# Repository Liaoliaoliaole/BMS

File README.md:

# BMS

# Project Structure

This repository contains the following directories to organize various aspects of the Battery Management System (BMS) project:
Meeting note and scrum report for scrum could be found from [Jira](https://liyuanliull.atlassian.net/jira/software/projects/SCRUM/boards/1/reports).

# `firmware`
The firmware directory includes the BMSServerApp source code. This application runs on the STM32L152RE Nucleo development board.   

## Cross-compilation
### Preconditions:
On Windows:   
- CMake
- Ninja
- STSW-LINK007
- GCC ARM None EABI Compiler

Details of the environment setup can be found in Confluence: [How-To-CrossCompile-BMSServerApp](https://liyuanliull.atlassian.net/wiki/spaces/BMSDEVELOP/pages/426109/How-to+Set+Up+Environment+and+Building+the+BMSServerApp)

### Build scripts
Navigate to the directory where the build script exists.   
Execute the following command in the terminal (such as Windows PowerShell):  
`./build_BMSServerApp.ps1 [-TestBuild]`   

- **Test Build**: Add the optional `-TestBuild` flag to include the testing features in your build, which will enable mock components or extra diagnostics during testing. For example:  
  `./build_BMSServerApp.ps1 -TestBuild`

Then connect the STM32L152RE to your PC, and run:    
`st-flash write BMSServerApp\build\BMSServerApp.bin 0x08000000`   

To remove the build, remove the `build` directory.

## GitHub Actions for CI/CD
The BMSServerApp project also supports automated builds via GitHub Actions. This allows you to build the project in the cloud whenever changes are pushed to the specified branch or a pull request is made.

### Build Types in GitHub Actions:
- The workflow is configured to build three different types: **Debug**, **Release**, and **Test**.
- The **Test** build defines a special `TEST` macro during compilation, enabling mock data and diagnostic features.

### How to Use GitHub Actions:
- **Trigger a Build**: Any push or pull request to the specified branch will automatically trigger the build process.
- **Check Build Status**: Monitor the status of the build in the "Actions" tab of the GitHub repository.
- **Find the Output**:   
  1. Click on the "Actions" tab.
  2. Select the Workflow Run: Find the specific workflow run to view its details.
  3. Scroll down to the "Artifacts" section on the workflow run page. This section shows the files that were uploaded during the workflow execution.
  4. Download the Binary File:  Click on the link for the binary file you want to download (e.g., `BMSServerApp-Debug-bin`, `BMSServerApp-Release-bin`, or `BMSServerApp-Test-bin`).   

# `prototyping`
This directory contains code, configurations, and other resources related to early-stage prototyping of the BMS project. It is used for experimenting with features, creating proof-of-concept implementations, and testing ideas before moving to production.  

- **Breadboard Prototyping**: The breadboard setup for the [current measurement module](https://liyuanliull.atlassian.net/wiki/spaces/BMSDEVELOP/pages/6520833/Voltage+Temperature+and+Current+measurement+Overview) and [temperature measurement prototypes](https://liyuanliull.atlassian.net/wiki/spaces/BMSDEVELOP/pages/8257538/Temperature+Measurement+Module+Prototyping+Documentation.) are stored in confluence.   
- **Calibration Functions**: Software calibration functions are developed to accommodate real-world measurements from the hardware prototypes, especially for [current mesurement](https://liyuanliull.atlassian.net/wiki/spaces/BMSDEVELOP/pages/19791874/Current+measurement+prototyping+and+calibration+calculation).   
Detailed documentation can be found in Confluence.  

# `schematic`
The schematic directory contains electrical and hardware design files, including circuit layouts, component schematics, and PCB designs. These designs are created using KiCad 7.0 and include PCB design files as well. All hardware-related files are stored here for reference.   

# `simulation`
This folder contains simulation models, scripts, and testing environments used for validating the BMS design and performance before physical implementation. Files related to simulation tools, test cases, and results are stored here.   

LTSpice Simulations: Simulation files created in LTSpice are used to validate the electrical design prior to prototyping.   

# `test`
This directory contains both hardware and software test cases and configurations for validating the BMS system.   

**Hardware Testing**: Includes [test cases](https://liyuanliull.atlassian.net/wiki/spaces/BMSDEVELOP/pages/20250626/Hardware+testing+notes) and documentation for validating the physical components of the BMS system: mosfet board, main board, current measurement board and temperature measurement board.   

**Software Testing**: The software testing for the BMSServerApp and BMSClientApp was conducted using several approaches to ensure robust functionality and communication. Key testing scenarios include:     
- ADC Converter Testing: Simulated mock ADC values to validate the proper functioning of the ADC conversion process in the software, ensuring accurate data handling.   
- Modbus Communication Testing: Tested Modbus function code 04 to verify reliable communication between the server and client, ensuring proper data exchange over the Modbus protocol.   
- Grafana Visualization: Validated the integration with Grafana by verifying the display of MCU-sent values on the Grafana dashboard, ensuring accurate and real-time monitoring of system metrics.   
- MOSFET Control Scenarios: Tested various MOSFET control scenarios by simulating different voltage, current, and temperature conditions. This validated the software's ability to control MOSFETs based on these parameters, ensuring correct operation under varying environmental and system conditions.

Detailed results of these hardware and software tests can be found in test dir README.

# `views`
The BMS project uses Grafana for visualization. A short documentation on how to log in and set up Grafana dashboards for monitoring BMS metrics is provided.

### How to Use Grafana

**Logging in as Guest**
1. Access Grafana: Open your web browser and navigate to the [Grafana URL](http://16.16.145.115:3000/login).
2. Guest Login: On the login page use username *Grafana_Viewer* and password *8qr8MzZM*.
3. Browse Dashboards: As a guest, you will have read-only access to the dashboards. You can browse through the available visualizations, interact with the data by zooming in on graphs, and apply filters to view specific data ranges.

**Logging in as Admin**
1. Access Grafana: Open your web browser and navigate to the [Grafana URL](http://16.16.145.115:3000/login).
2. Admin Login: Enter the admin username and password. You can obtain this data on request.
3. Admin Dashboard: Once logged in, you will have full access to all Grafana features, including the ability to create, edit, and delete dashboards, manage data sources, and configure system settings.

**Adding New Visualizations**
1. Add a Panel: Click on "Add new panel" to start creating a new visualization.
2. Select Data Source: Choose the data source from which you want to pull data. This is BMS database in our case.
3. Configure Query: Write the query to fetch the data you need. 
4. Choose Visualization Type: Select the type of visualization you want to create, such as a graph, table or heatmap.
5. Save the Panel: Once you are satisfied with the configuration, click "Apply" to add the panel to your dashboard. Don't forget to save the dashboard itself to retain your changes.

### Testing

**For Test Purposes with Static Values Compile BMSServerApp (STM32) with Symbol TEST**

1. Open the BMSServerApp project in your IDE.
2. Locate the project settings where preprocessor symbols are defined. This is typically found under project properties or build settings.
3. Add the symbol `TEST` to the list of preprocessor definitions.
4. Build the project. This will generate the firmware binary with the test mode enabled.
5. Flash the compiled firmware onto the STM32 microcontroller using a programmer or debugger tool.
6. With the test firmware running, the BMSServerApp will use predefined static values instead of real sensor data, allowing you to test the system's functionality without needing actual sensor inputs.

**For Testing Grafana Without Using STM32 Run `test_data_generator.py` from Views Folder**

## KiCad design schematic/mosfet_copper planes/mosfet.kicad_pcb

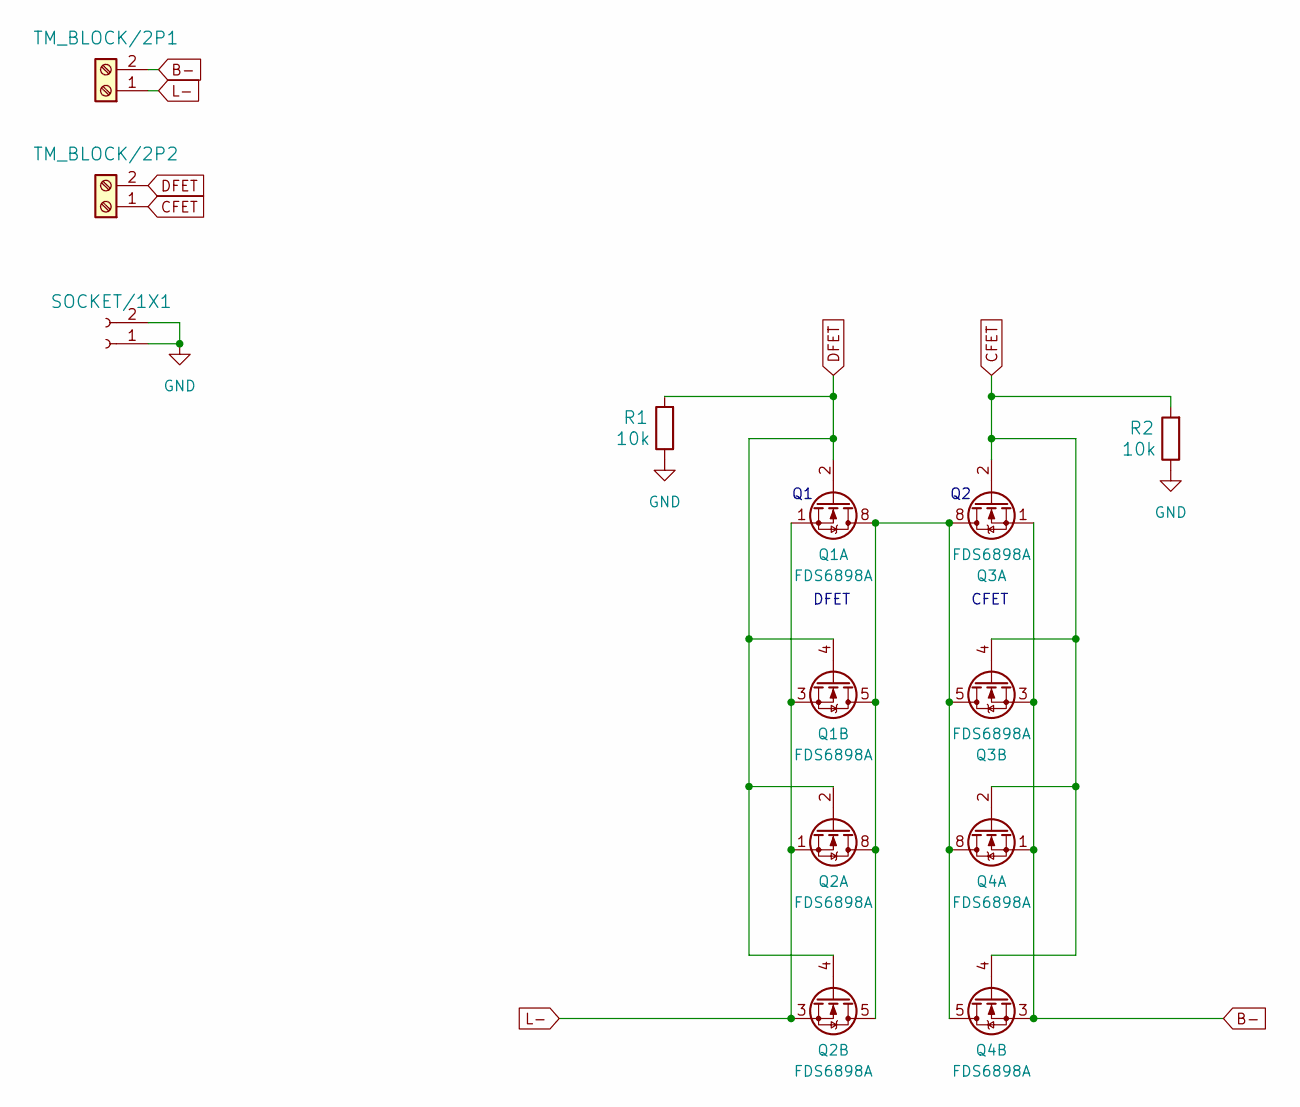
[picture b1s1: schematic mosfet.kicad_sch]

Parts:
Q1, Q2, Q3, Q4: FDS6898A; SOIC-8_3.9x4.9mm_P1.27mm
R1, R2: 10k; 1206; Tolerance +-5%
SOCKET/1X1: SOCKET_1X2; SOCKET_1x2
TM_BLOCK/2P1, TM_BLOCK/2P2: TM_BLOCK_2P

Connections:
B-: Q3.1 (S1), Q3.3 (S2), Q4.1 (S1), Q4.3 (S2), TM_BLOCK/2P1.2
CFET: Q3.2 (G1), Q3.4 (G2), Q4.2 (G1), Q4.4 (G2), R2.2, TM_BLOCK/2P2.1
DFET: Q1.2 (G1), Q1.4 (G2), Q2.2 (G1), Q2.4 (G2), R1.2, TM_BLOCK/2P2.2
GND: R1.1, R2.1, SOCKET/1X1.1, SOCKET/1X1.2
L-: Q1.1 (S1), Q1.3 (S2), Q2.1 (S1), Q2.3 (S2), TM_BLOCK/2P1.1
unnamed: Q1.5 (D2), Q1.6 (D2), Q1.7 (D1), Q1.8 (D1), Q2.5 (D2), Q2.6 (D2), Q2.7 (D1), Q2.8 (D1), Q3.5 (D2), Q3.6 (D2), Q3.7 (D1), Q3.8 (D1), Q4.5 (D2), Q4.6 (D2), Q4.7 (D1), Q4.8 (D1)

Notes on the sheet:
DFET
CFET

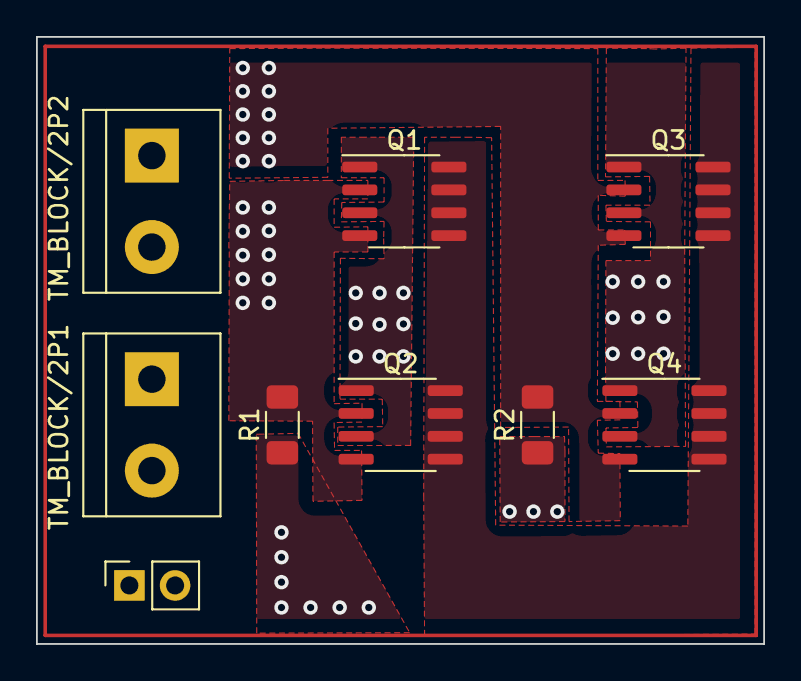
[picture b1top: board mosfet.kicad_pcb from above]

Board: 2 copper layers, 40.4 x 33.7 mm, 9 parts (0 on the bottom side), 6 nets.

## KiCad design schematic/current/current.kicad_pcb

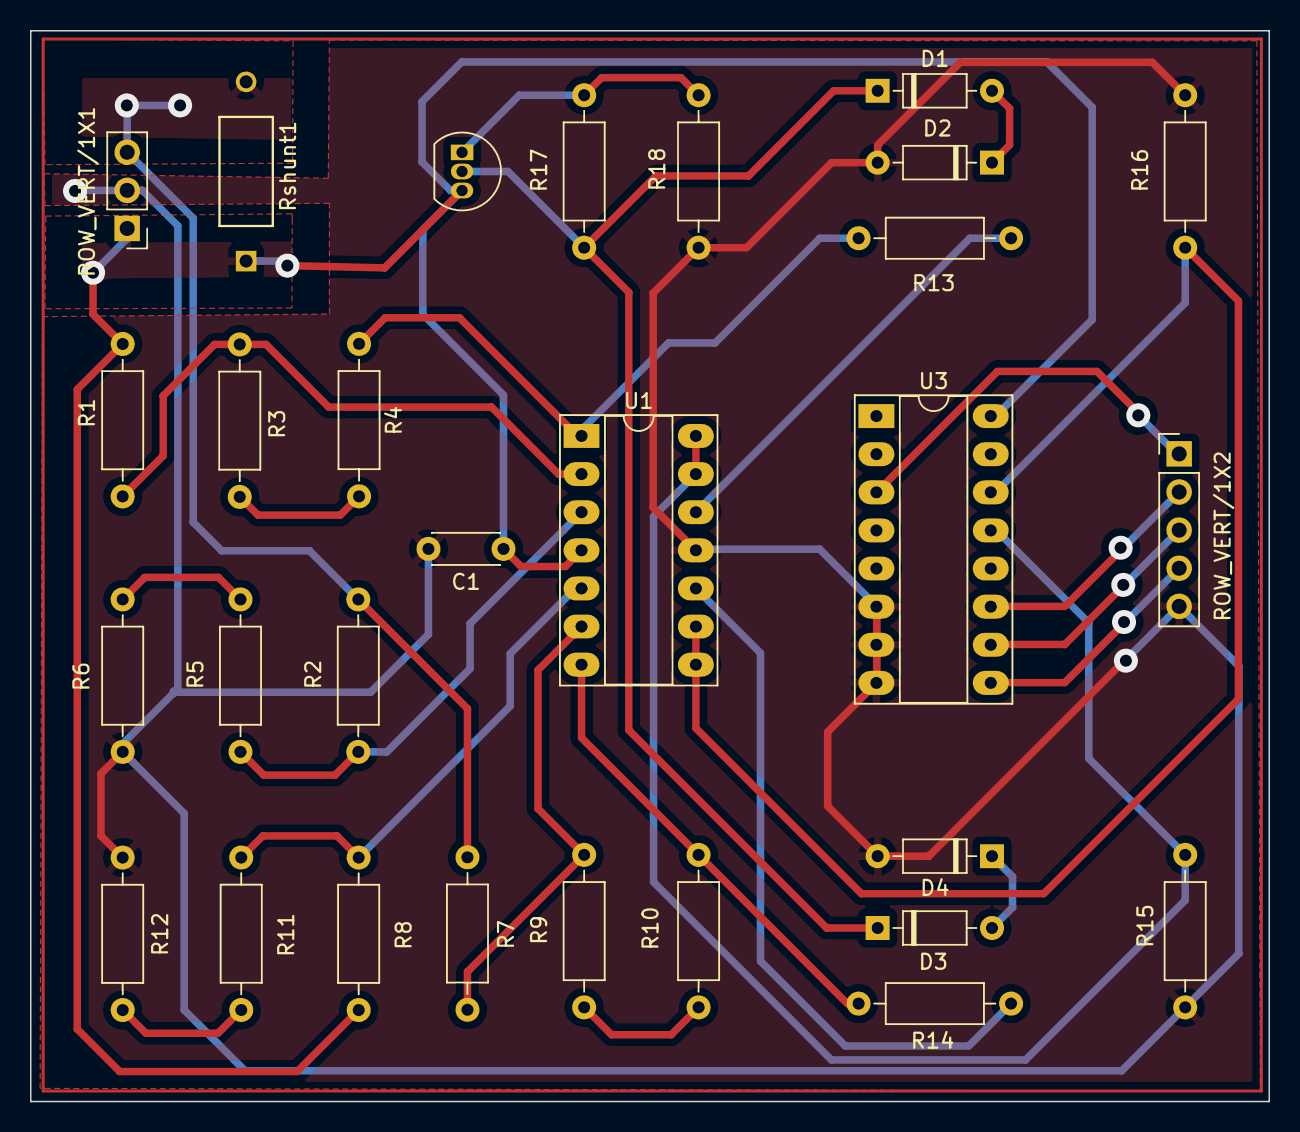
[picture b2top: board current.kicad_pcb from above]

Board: 2 copper layers, 82.5 x 71.4 mm, 29 parts (0 on the bottom side), 25 nets.

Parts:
C1: 100NF_50V_CER; C5_0
D1, D2, D3, D4: 1N4148; D_DO-35_SOD27_P7.62mm_Horizontal
R1, R2, R7, R8: 910R; R3_5W
R3, R5, R9, R11: 30k; R3_5W
R4, R6, R10, R12: 2k; R3_5W
R13, R14, R15, R16: 10k; R3_5W
R17: 470R; R3_5W
R18: 620R; R3_5W
ROW_VERT/1X1: ROW_VERT_1X3; ROW_VERT_1x3
ROW_VERT/1X2: ROW_VERT_1X5; ROW_VERT_1x5
Rshunt1: 0.01R; RES_WH&slash_NB_OHM
U1: LM324NE4; DIP-14_W7.62mm_Socket_LongPads
U2: LM317L_TO92; TO-92_Inline
U3: CD4051B; DIP-16_W7.62mm_Socket_LongPads

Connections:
+12V: C1.1, R1.1, R8.1, ROW_VERT/1X1.1, Rshunt1.1, U1.4, U2.3 (VI), U3.16 (VDD)
B+: R2.1, R7.1, ROW_VERT/1X1.3, Rshunt1.2
GND: C1.2, D2.2 (A), D4.2 (A), R6.1, R12.1, R15.1, R16.1, R18.1, ROW_VERT/1X1.2, ROW_VERT/1X2.5, U1.11, U3.6 (INH), U3.7 (VEE), U3.8 (VSS)
unnamed: D1.2 (A), D2.1 (K)
unnamed: D3.2 (A), D4.1 (K)
unnamed: R1.2, R3.1, U1.2
unnamed: R2.2, R5.2, U1.3
unnamed: R3.2, R4.1
unnamed: R5.1, R6.2
unnamed: R7.2, R9.1, U1.6
unnamed: R9.2, R10.1
unnamed: R11.1, R12.2
unnamed: R8.2, R11.2, U1.5
unnamed: R13.2, U1.12
unnamed: R14.2, U1.10
unnamed: R17.1, R18.2, U2.1 (ADJ)
unnamed: R15.2, U1.13, U1.14, U3.13 (X0)
unnamed: R16.2, U1.8, U1.9, U3.14 (X1)
V_ESD: D1.1 (K), D3.1 (K), R17.2, U2.2 (VO)
V_shunt: ROW_VERT/1X2.1, U3.3 (X)
V_shunt1: R4.2, R13.1, U1.1
V_shunt2: R10.2, R14.1, U1.7
sel_A: ROW_VERT/1X2.2, U3.11 (A)
sel_B: ROW_VERT/1X2.3, U3.10 (B)
sel_C: ROW_VERT/1X2.4, U3.9 (C)

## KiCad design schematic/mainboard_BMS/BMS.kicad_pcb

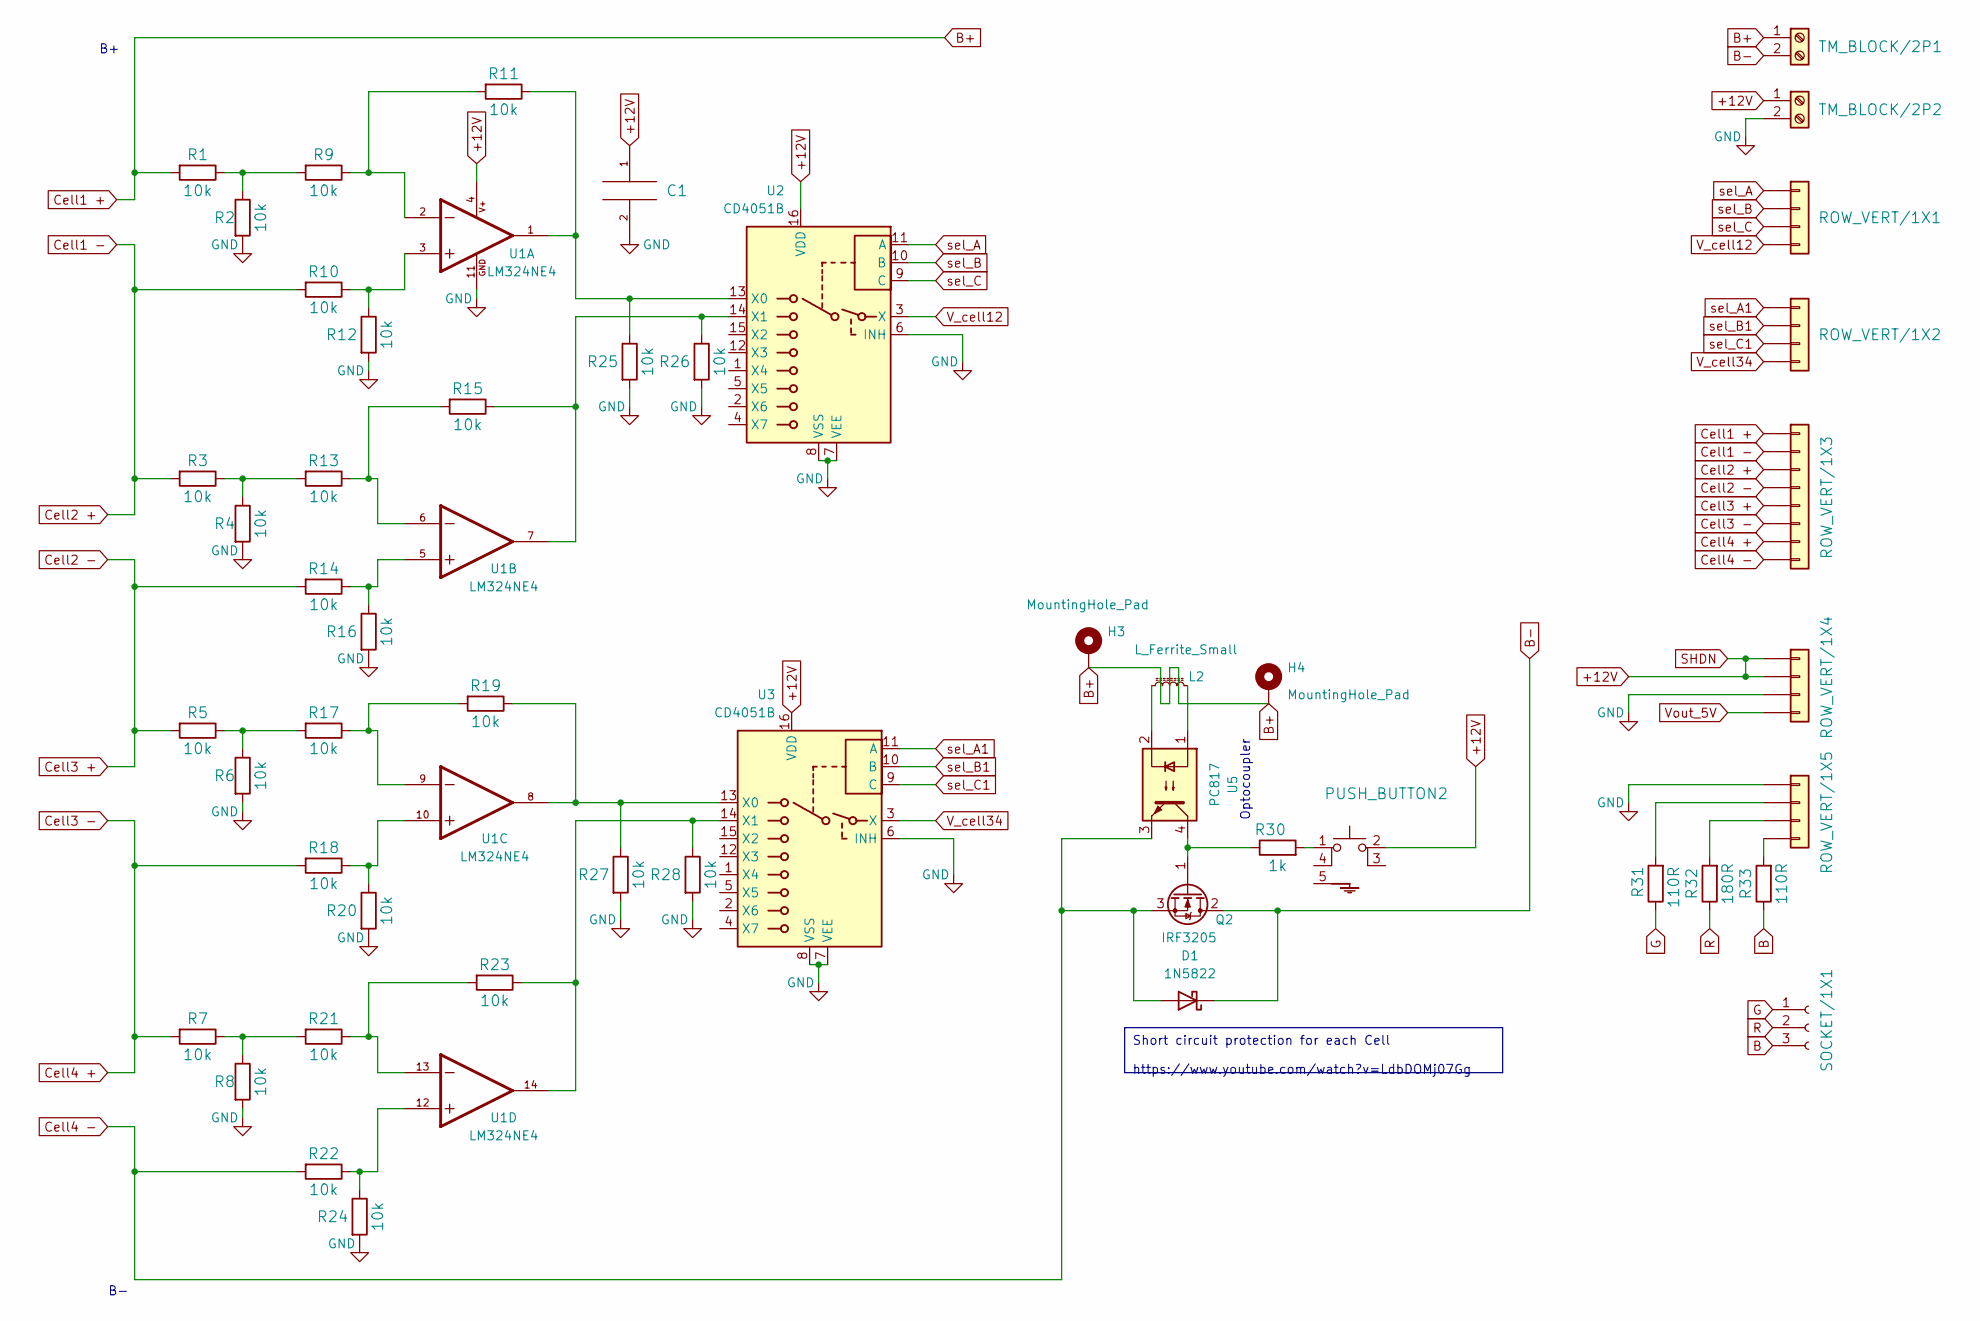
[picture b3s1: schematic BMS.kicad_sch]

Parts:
C1: 100NF_50V_CER; C5_0; Tolerance +-10%
D1: 1N5822; D_DO-201AD_P15.24mm_Horizontal
H3, H4: MountingHole_Pad; MountingHole_2.2mm_M2_Pad
L2: L_Ferrite_Small; PE92112KNL
PUSH_BUTTON2: PUSH_BUTTON; SKHHQV
Q2: IRF3205; TO-220-3_Vertical
R1, R2, R3, R4, R5, R6, R7, R8, R9, R10, R11, R12, R13, R14, R15, R16, R17, R18, R19, R20, R21, R22, R23, R24, R25, R26, R27, R28: 10k; R3_5W; Tolerance +-1%
R30: 1k; R3_5W; Tolerance +-1%
R31, R33: 110R; R3_5W; Tolerance +-1%
R32: 180R; R3_5W; Tolerance +-1%
ROW_VERT/1X1, ROW_VERT/1X2, ROW_VERT/1X4, ROW_VERT/1X5: ROW_VERT_1X4; ROW_VERT_1x4
ROW_VERT/1X3: ROW_VERT_1X8; ROW_VERT_1x8
SOCKET/1X1: SOCKET_1X3; SOCKET_1x3
TM_BLOCK/2P1, TM_BLOCK/2P2: TM_BLOCK_2P
U1: LM324NE4; DIP-14_W7.62mm_Socket_LongPads; PARTREV D
U2, U3: CD4051B; DIP-16_W7.62mm_Socket_LongPads
U5: PC817; DIP-4_W7.62mm

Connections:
+12V: C1.1, PUSH_BUTTON2.2 (A), ROW_VERT/1X4.1, ROW_VERT/1X4.2, TM_BLOCK/2P2.1, U1.4, U2.16 (VDD), U3.16 (VDD)
B: R33.1, SOCKET/1X1.3
B+: H3.1, H4.1, R1.2, ROW_VERT/1X3.1, TM_BLOCK/2P1.1
B-: D1.1 (K), Q2.2 (D), TM_BLOCK/2P1.2
Cell1 -: R3.2, R10.2, ROW_VERT/1X3.2, ROW_VERT/1X3.3
Cell2 -: R5.2, R14.2, ROW_VERT/1X3.4, ROW_VERT/1X3.5
Cell3 -: R7.2, R18.2, ROW_VERT/1X3.6, ROW_VERT/1X3.7
Cell4 -: D1.2 (A), Q2.3 (S), R22.2, ROW_VERT/1X3.8, U5.3
G: R31.1, SOCKET/1X1.1
GND: C1.2, R2.2, R4.2, R6.2, R8.2, R12.2, R16.2, R20.2, R24.2, R25.2, R26.2, R27.2, R28.2, ROW_VERT/1X4.3, ROW_VERT/1X5.1, TM_BLOCK/2P2.2, U1.11, U2.6 (INH), U2.7 (VEE), U2.8 (VSS), U3.6 (INH), U3.7 (VEE), U3.8 (VSS)
unnamed: L2.1, U5.2
unnamed: L2.2, U5.1
unnamed: PUSH_BUTTON2.1, R30.2
unnamed: Q2.1 (G), R30.1, U5.4
unnamed: R1.1, R2.1, R9.2
unnamed: R10.1, R12.1, U1.3
unnamed: R9.1, R11.2, U1.2
unnamed: R13.1, R15.2, U1.6
unnamed: R3.1, R4.1, R13.2
unnamed: R14.1, R16.1, U1.5
unnamed: R17.1, R19.2, U1.9
unnamed: R5.1, R6.1, R17.2
unnamed: R18.1, R20.1, U1.10
unnamed: R21.1, R23.2, U1.13
unnamed: R7.1, R8.1, R21.2
unnamed: R22.1, R24.1, U1.12
unnamed: R31.2, ROW_VERT/1X5.2
unnamed: R32.2, ROW_VERT/1X5.3
unnamed: R33.2, ROW_VERT/1X5.4
unnamed: R11.1, R25.1, U1.1, U2.13 (X0)
unnamed: R15.1, R26.1, U1.7, U2.14 (X1)
unnamed: R19.1, R27.1, U1.8, U3.13 (X0)
unnamed: R23.1, R28.1, U1.14, U3.14 (X1)
R: R32.1, SOCKET/1X1.2
V_cell12: ROW_VERT/1X1.4, U2.3 (X)
V_cell34: ROW_VERT/1X2.4, U3.3 (X)
Vout_5V: ROW_VERT/1X4.4
sel_A: ROW_VERT/1X1.1, U2.11 (A)
sel_A1: ROW_VERT/1X2.1, U3.11 (A)
sel_B: ROW_VERT/1X1.2, U2.10 (B)
sel_B1: ROW_VERT/1X2.2, U3.10 (B)
sel_C: ROW_VERT/1X1.3, U2.9 (C)
sel_C1: ROW_VERT/1X2.3, U3.9 (C)

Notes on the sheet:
Short circuit protection for each Cell https://www.youtube.com/watch?v=LdbDOMj07Gg
Optocoupler

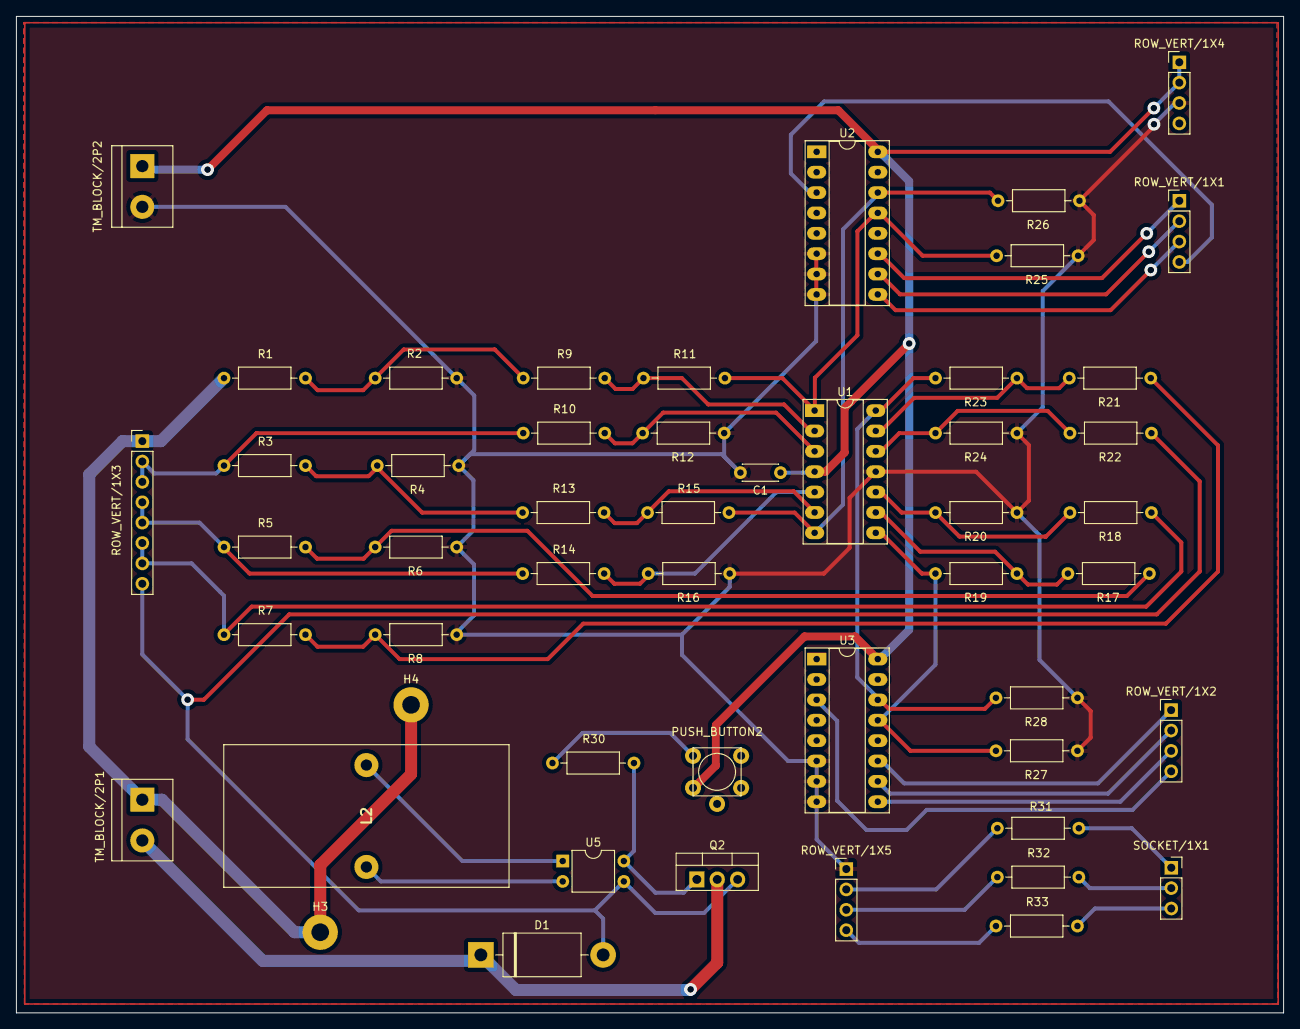
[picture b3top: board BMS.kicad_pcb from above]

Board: 2 copper layers, 158.0 x 124.2 mm, 51 parts (0 on the bottom side), 42 nets.

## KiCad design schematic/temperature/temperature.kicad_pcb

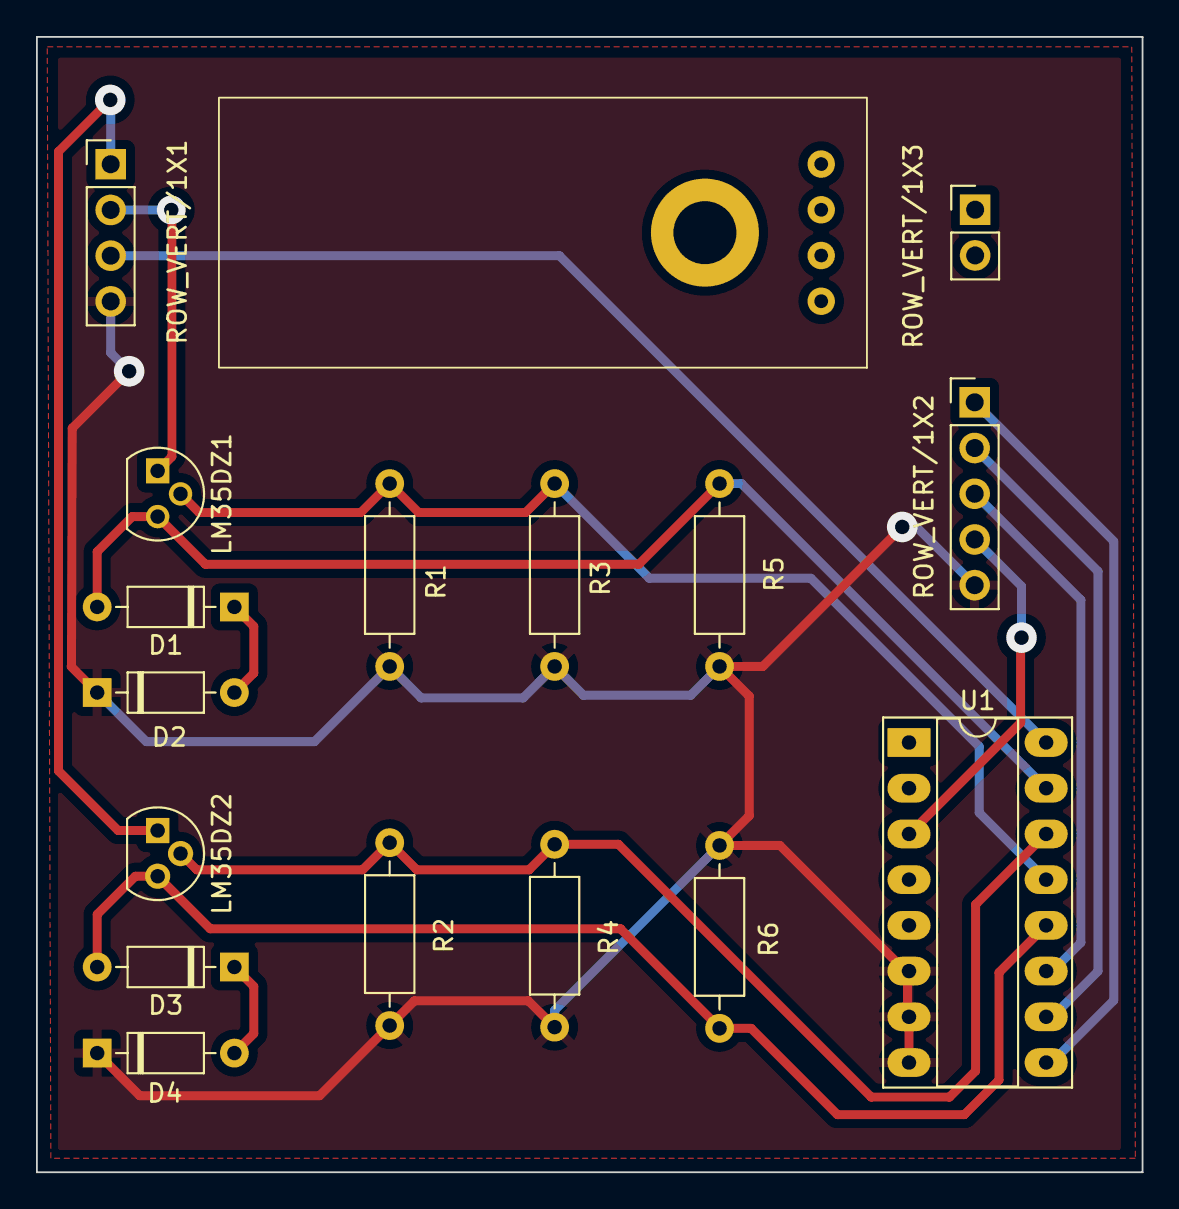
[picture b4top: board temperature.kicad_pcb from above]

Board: 2 copper layers, 61.4 x 63.1 mm, 17 parts (0 on the bottom side), 14 nets.

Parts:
A1: Flame_KY026; KY026
D1, D2, D3, D4: 1N4148; D_DO-35_SOD27_P7.62mm_Horizontal
LM35DZ1, LM35DZ2: LM35DZ_TO92; TO-92
R1, R2: 18k; R3_5W
R3, R4, R5, R6: 10k; R3_5W
ROW_VERT/1X1: ROW_VERT_1X4; ROW_VERT_1x4
ROW_VERT/1X2: ROW_VERT_1X5; ROW_VERT_1x5
ROW_VERT/1X3: ROW_VERT_1X2; ROW_VERT_1x2
U1: CD4051B; DIP-16_W7.62mm_Socket_LongPads

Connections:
+5V: ROW_VERT/1X1.3, U1.16 (VDD)
GND: D2.1 (K), D4.1 (K), R1.1, R2.1, R3.1, R4.1, R5.1, R6.1, ROW_VERT/1X1.4, ROW_VERT/1X2.5, U1.6 (INH), U1.7 (VEE), U1.8 (VSS)
unnamed: D1.2 (A), LM35DZ1.3 (GND), R5.2, U1.15 (X2)
unnamed: D1.1 (K), D2.2 (A)
unnamed: D3.2 (A), LM35DZ2.3 (GND), R6.2, U1.12 (X3)
unnamed: D3.1 (K), D4.2 (A)
unnamed: LM35DZ1.2 (Vout), R1.2, R3.2, U1.13 (X0)
unnamed: LM35DZ2.2 (Vout), R2.2, R4.2, U1.14 (X1)
V_cell12: LM35DZ1.1 (+VS), ROW_VERT/1X1.2
V_cell34: LM35DZ2.1 (+VS), ROW_VERT/1X1.1
V_temperature: ROW_VERT/1X2.4, U1.3 (X)
sel_A: ROW_VERT/1X2.3, U1.11 (A)
sel_B: ROW_VERT/1X2.2, U1.10 (B)
sel_C: ROW_VERT/1X2.1, U1.9 (C)

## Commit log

2024-09-08 Initial project structure setup
2024-09-08 Initialized bms project in truestudio.
    Issue : SCRUM-7
2024-09-09 SCRUM-6 Added a text file
2024-09-09 Meta info SCRUM-7
2024-09-09 Add test. Issue : SCRUM-5
2024-09-09 block diagram
2024-09-09 SCRUM-6 Text file added
2024-09-09 Ignore files in firmware/.metadata/. Add basic libs of stm32 functions.
    Issue : SCRUM-7
2024-09-09 SCRUM-5 add active balancing
2024-09-09 active balancing
2024-09-10 SCRUM-5 test
2024-09-10 Add LM324N opamp prototypying. Designed calibration method.
    Issue : SCRUM-5
2024-09-14 Add modbus slave lib, update ADC convert.
    Issue: SCRUM-7
2024-09-17 Add main supporting mock values using modbus RTU Function code 04 to communicate with test_slave. Add test_slave. Restructure include, src and libs.
    Issue: SCRUM-7
2024-09-18 Add multiplexer code. Tested with PA5 led blink to select channal. Issue: SCRUM-7
2024-09-19 active_balancing.jpg
2024-09-19 SCRUM-2 add draft schematic
2024-09-19 SCRUM-6 Added a python prototype file for grafana usage
2024-09-19 SCRUM-5 add new block diagram
2024-09-21 Create cross-compilation steps using cmake and ninja. Updated README for relevant changes.
    Issue: SCRUM-15
2024-09-22 Add build script. SCRUM-15
2024-09-22 Updated README with build scripts instruction.
    ISSUE: SCRUM-15
2024-09-22 Add code draft for integration and testing. ISSUE: SCRUM-15
2024-09-25 Add adc basic and adc_converter. Add mock adc value testing. SCRUM-19
2024-09-27 SCRUM-2-add schematics for 4 modules
2024-09-27 Add LM35 prototyping test code.
2024-09-27 Add LM35 prototyping result.
2024-09-27 Rename Capture.PNG to Capture_lm35_test.PNG
2024-09-27 temperory statsh.
2024-09-27 Add temperature measurement prototyping documentation.
2024-09-28 Restructured modbus header and src file. Modified tempereature sensor adc converter. SCRUM-19
2024-09-28 Updated gitignore file.
2024-09-28 Update .gitignore to exclude build and .vscode directories
2024-09-29 Updated yml to support only in this branch. SCRUM-20
2024-10-02 Create test_current_meas
    Initial test code for shunt resistor measurement of current.
2024-10-04 SCRUM-10 Edited Nucle code - Added 1 more senfing value. Edited master code - added mysql usage
2024-10-05 Depreciated this test code.
2024-10-05 Merged main. SCRUM-20
2024-10-05 Modify back main branch build automation yml. Do not modify this file.
2024-10-05 Add automation build in gitignore.
2024-10-06 Refactor adc, mux, modbus and sytem pin configuration. Seperated TEST build. SCRUM-20
2024-10-06 Update git ignore.
2024-10-06 Correct cmakelists and build script, tested locally succeeded. SCRUM-20
2024-10-06 Init implementation of mosfet control logic. SCRUM-20
2024-10-06 add new schematics for 4 modules, pcb layout of mosfet and current simulation
2024-10-12 Update mosfet control logic supporting overcurrent overtemperature overvoltage shortcircuit and over diode current. Init mosfet control test. SCRUM-20
2024-10-13 Add mosfet control tests. SCRUM-20
2024-10-13 Update mosfet_control logic using bit mask for fault mask. SCRUM-20
2024-10-20 Add mutiplexer select logic to read adc according to different module hardware design. SCRUM-14
2024-10-20 Replaced float calculation by all interger calculation. Applied moving average filter for adc read values. Added function declare and introduction. Init intergration test, tobe continue. SCRUM-14
2024-11-01 robot framework that for now just tests if the board is running and a couple of files ang changes to let board communicate with robot framework using pyserial (as in task)
2024-11-01 Add deepsleep mode. Add actual current calibration number. SCRUM-14
2024-11-01 Scrum 14 design state machine integrated with mosfet control logic (#9)
    * Add mutiplexer select logic to read adc according
    to different module hardware design.
    SCRUM-14
    * Update cmake-multi-platform.yml
    * Update cmake-multi-platform.yml
    * Replaced float calculation by all interger calculation.
2024-11-03 Update body diode protection critical case. SCRUM-23
2024-11-03 Update actual implementation according to passed test suit for mosfet control. SCRUM-23
2024-11-18 upload temperature schematic
2024-11-19 SCRUM-2 add the updated schematics and simulation
2024-11-19 Update README.md
    Added information to views part
2024-11-19 Rename BMSClientApp.py to BMSClientApp_old.py
2024-11-19 Rename BMSClientApp_updated.py to BMSClientApp_old_updated.py
2024-11-19 Rename BMSClientApp_update_sql.py to BMSClientApp.py
2024-11-19 Scrum 2 create schematic for pcb (#11)
    * SCRUM-2-add schematics for 4 modules
    * add new schematics for 4 modules, pcb layout of mosfet and current simulation
    * upload temperature schematic
    * SCRUM-2 add the updated schematics and simulation
    ---------
